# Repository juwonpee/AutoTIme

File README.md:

# AutoTime

requirements: python 3.7</br>
*3.8 not supported*</br>
python3 pip -m git install eel</br>
python3 pip -m git install pymysql</br>
</br>
run engine.py

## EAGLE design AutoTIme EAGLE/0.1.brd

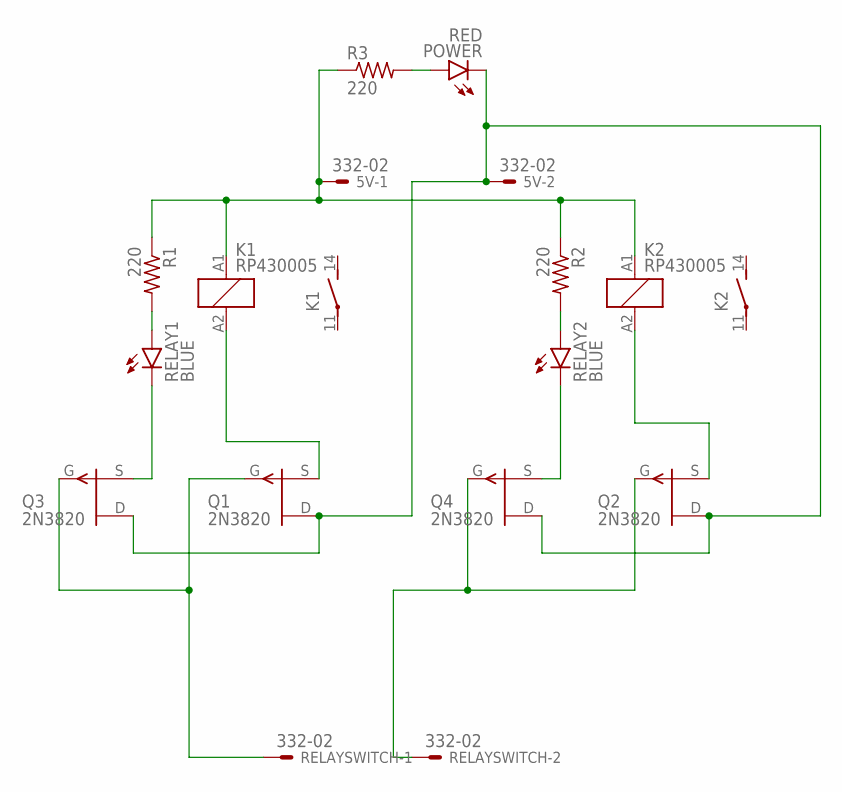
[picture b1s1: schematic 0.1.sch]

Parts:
5V: 332-02
K1, K2: RP430005; RT-N/O12A5
POWER: RED; LED5MM
Q1, Q2, Q3, Q4: 2N3820; TO92
R1, R2, R3: 220; 0204/7
RELAY1, RELAY2: BLUE; LED5MM
RELAYSWITCH: 332-02

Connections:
5V: 5V.1, K1.A1 (1), K2.A1 (1), R1.1, R2.1, R3.1
GROUND: 5V.2, POWER.K (C), Q1.3 (D), Q2.3 (D), Q3.3 (D), Q4.3 (D)
unnamed: K1.A2 (2), Q1.1 (S)
unnamed: K2.A2 (2), Q2.1 (S)
unnamed: Q3.1 (S), RELAY1.K (C)
unnamed: Q4.1 (S), RELAY2.K (C)
unnamed: POWER.A, R3.2
RELAYLED1: R1.2, RELAY1.A
RELAYLED2: R2.2, RELAY2.A
RELAYSWITCH1: Q1.2 (G), Q3.2 (G), RELAYSWITCH.1
RELAYSWITCH2: Q2.2 (G), Q4.2 (G), RELAYSWITCH.2

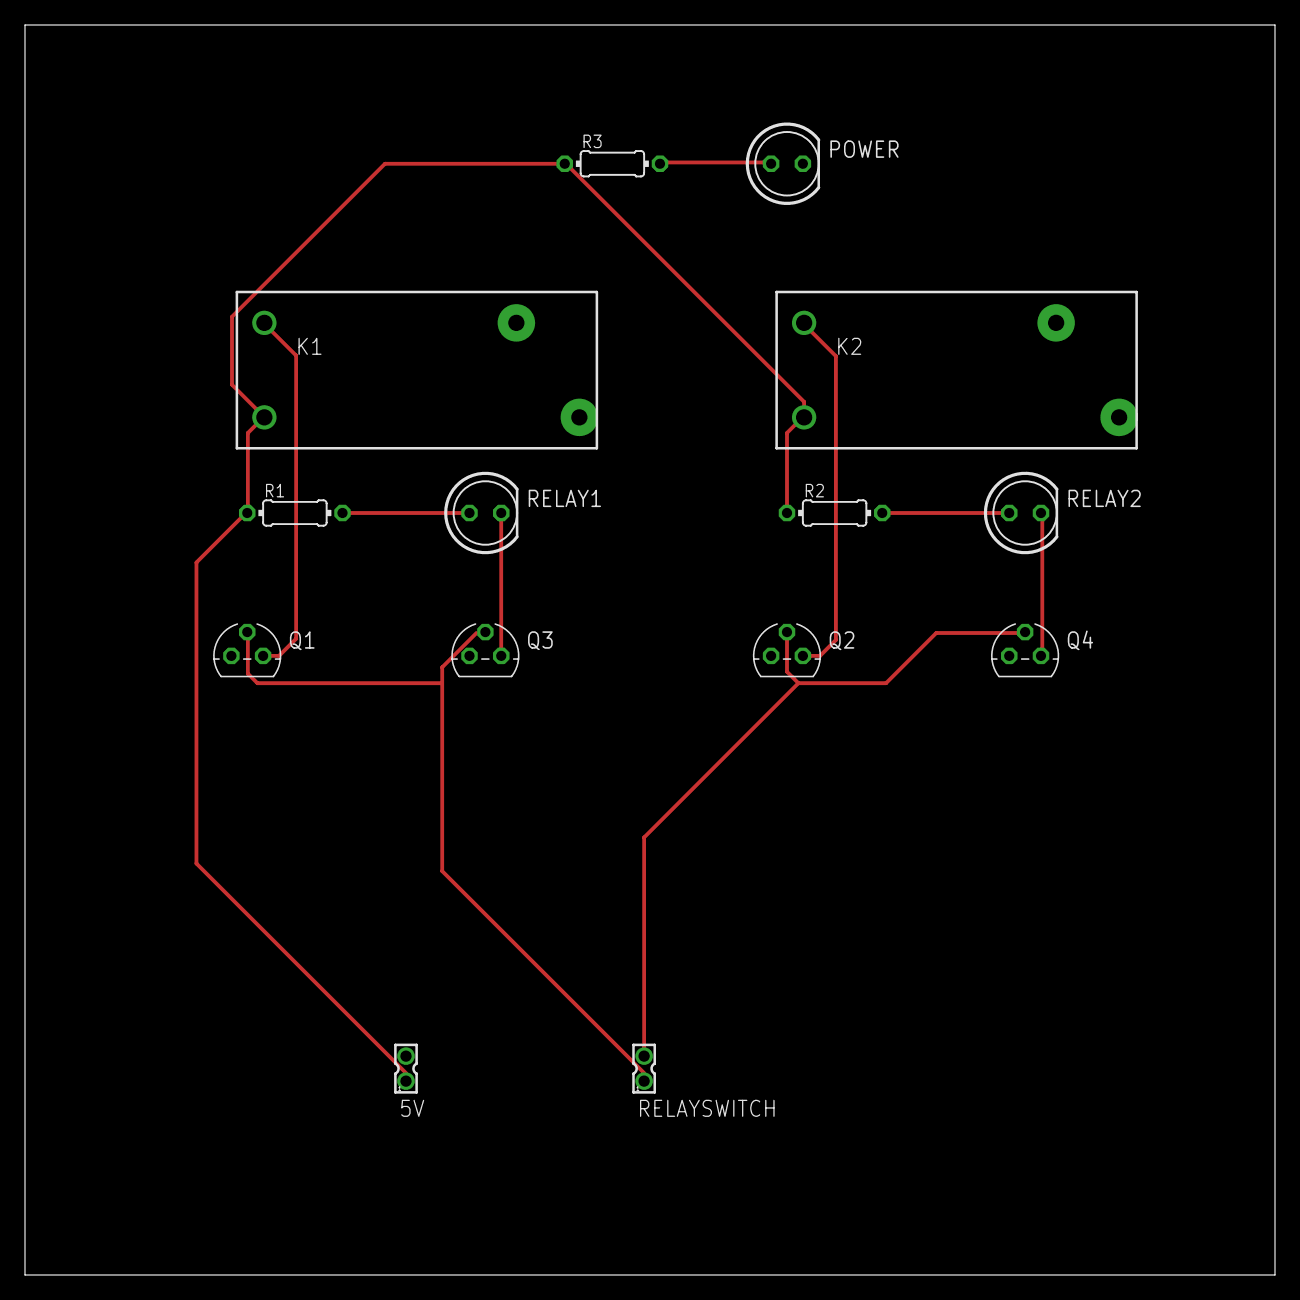
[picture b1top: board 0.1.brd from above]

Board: 2 copper layers, 100.0 x 100.0 mm, 14 parts (0 on the bottom side), 11 nets.

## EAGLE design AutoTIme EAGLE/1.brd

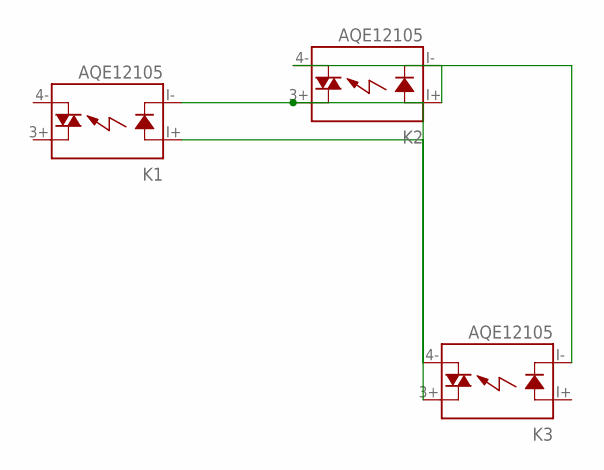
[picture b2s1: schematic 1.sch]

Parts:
K1, K2, K3: AQE12105; AQE

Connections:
unnamed: K1.I+ (A), K3.4- (DS2)
unnamed: K1.I- (K), K2.3+ (DS1), K3.3+ (DS1)
unnamed: K2.I+ (A), K2.I- (K)
unnamed: K2.4- (DS2), K3.I- (K)

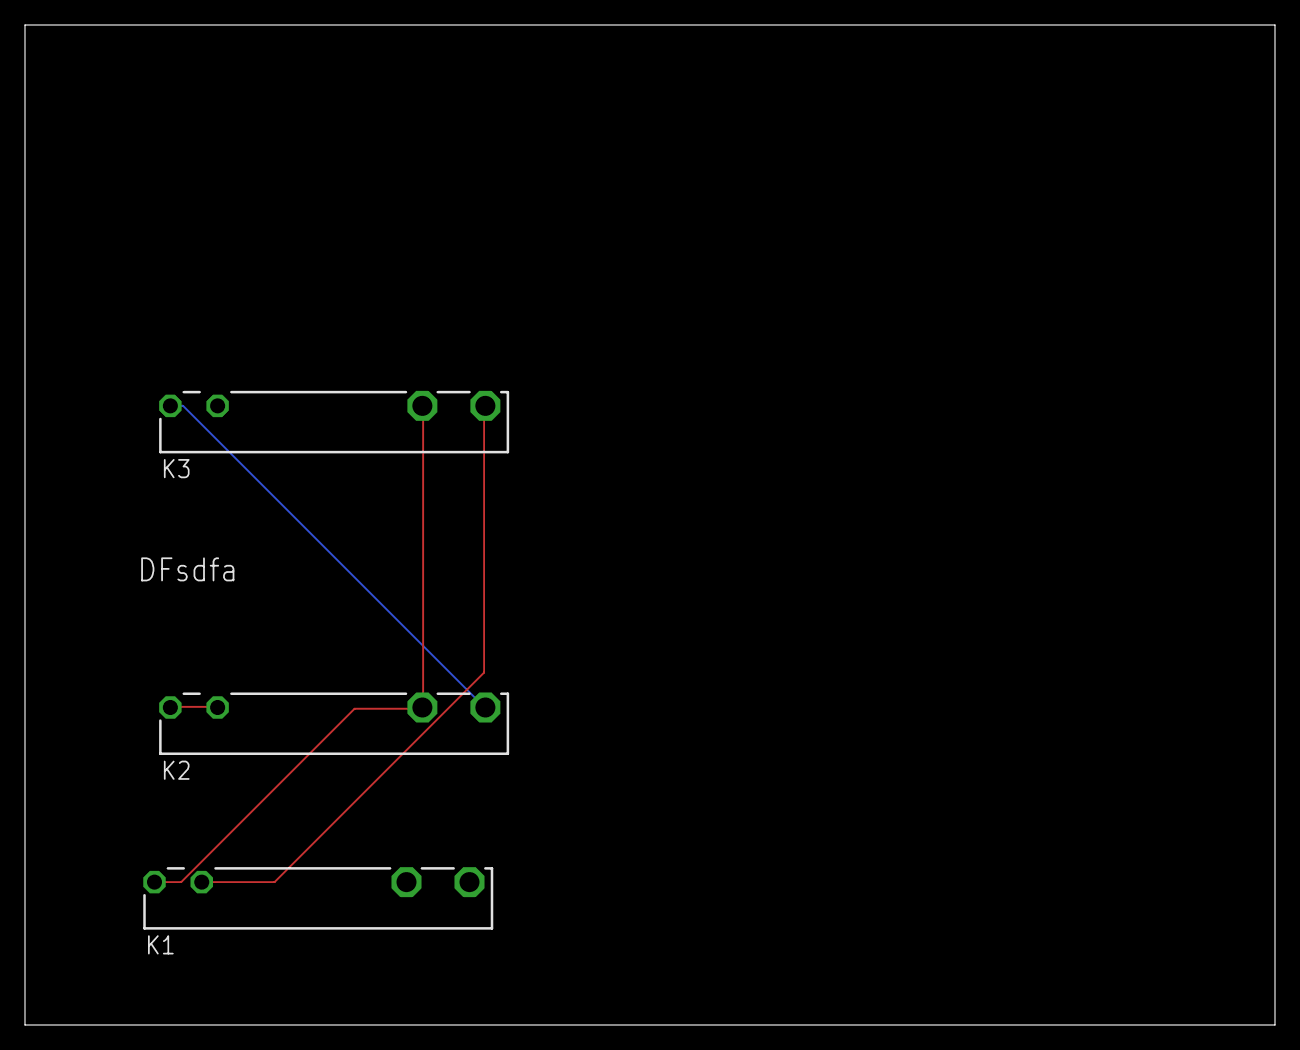
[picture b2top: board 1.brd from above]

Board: 2 copper layers, 100.0 x 80.0 mm, 3 parts (0 on the bottom side), 4 nets.

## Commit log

2019-05-20 aksdjflaskjdf
2019-05-20 dfgsdgsdds
2019-05-20 Test1
2019-05-20 dfgdfgdfgㅇㅀㅇㅀㅇㄹ
2019-07-29 보드 기본 기능들 더함
2019-08-27 basic
2019-10-08 Integration with server
2019-10-10 UI demo
2019-10-24 Basic working
2019-10-24 fix reset button
2019-10-28 fix offline
2019-10-29 거의 다 완성
    I\O 콘트롤만 추가하면 완성
2019-10-30 fix bug
    full screen mode and fix offline bug for item names
2019-10-30 implement server1030
2019-10-30 fonts
2019-10-30 gpio
2019-10-30 gpio fix
2019-11-02 added boot shell script
2019-11-02 avoid keyring
2019-11-05 test img
2019-11-06 font change
